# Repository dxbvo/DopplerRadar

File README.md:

# DopplerRadar
Development of a 24GHz Doppler radar system to measure the speed of a hockey puck. Developed using a STM32L476 Discovery board and a K-LC5 radar module from RFbeam Microwave.

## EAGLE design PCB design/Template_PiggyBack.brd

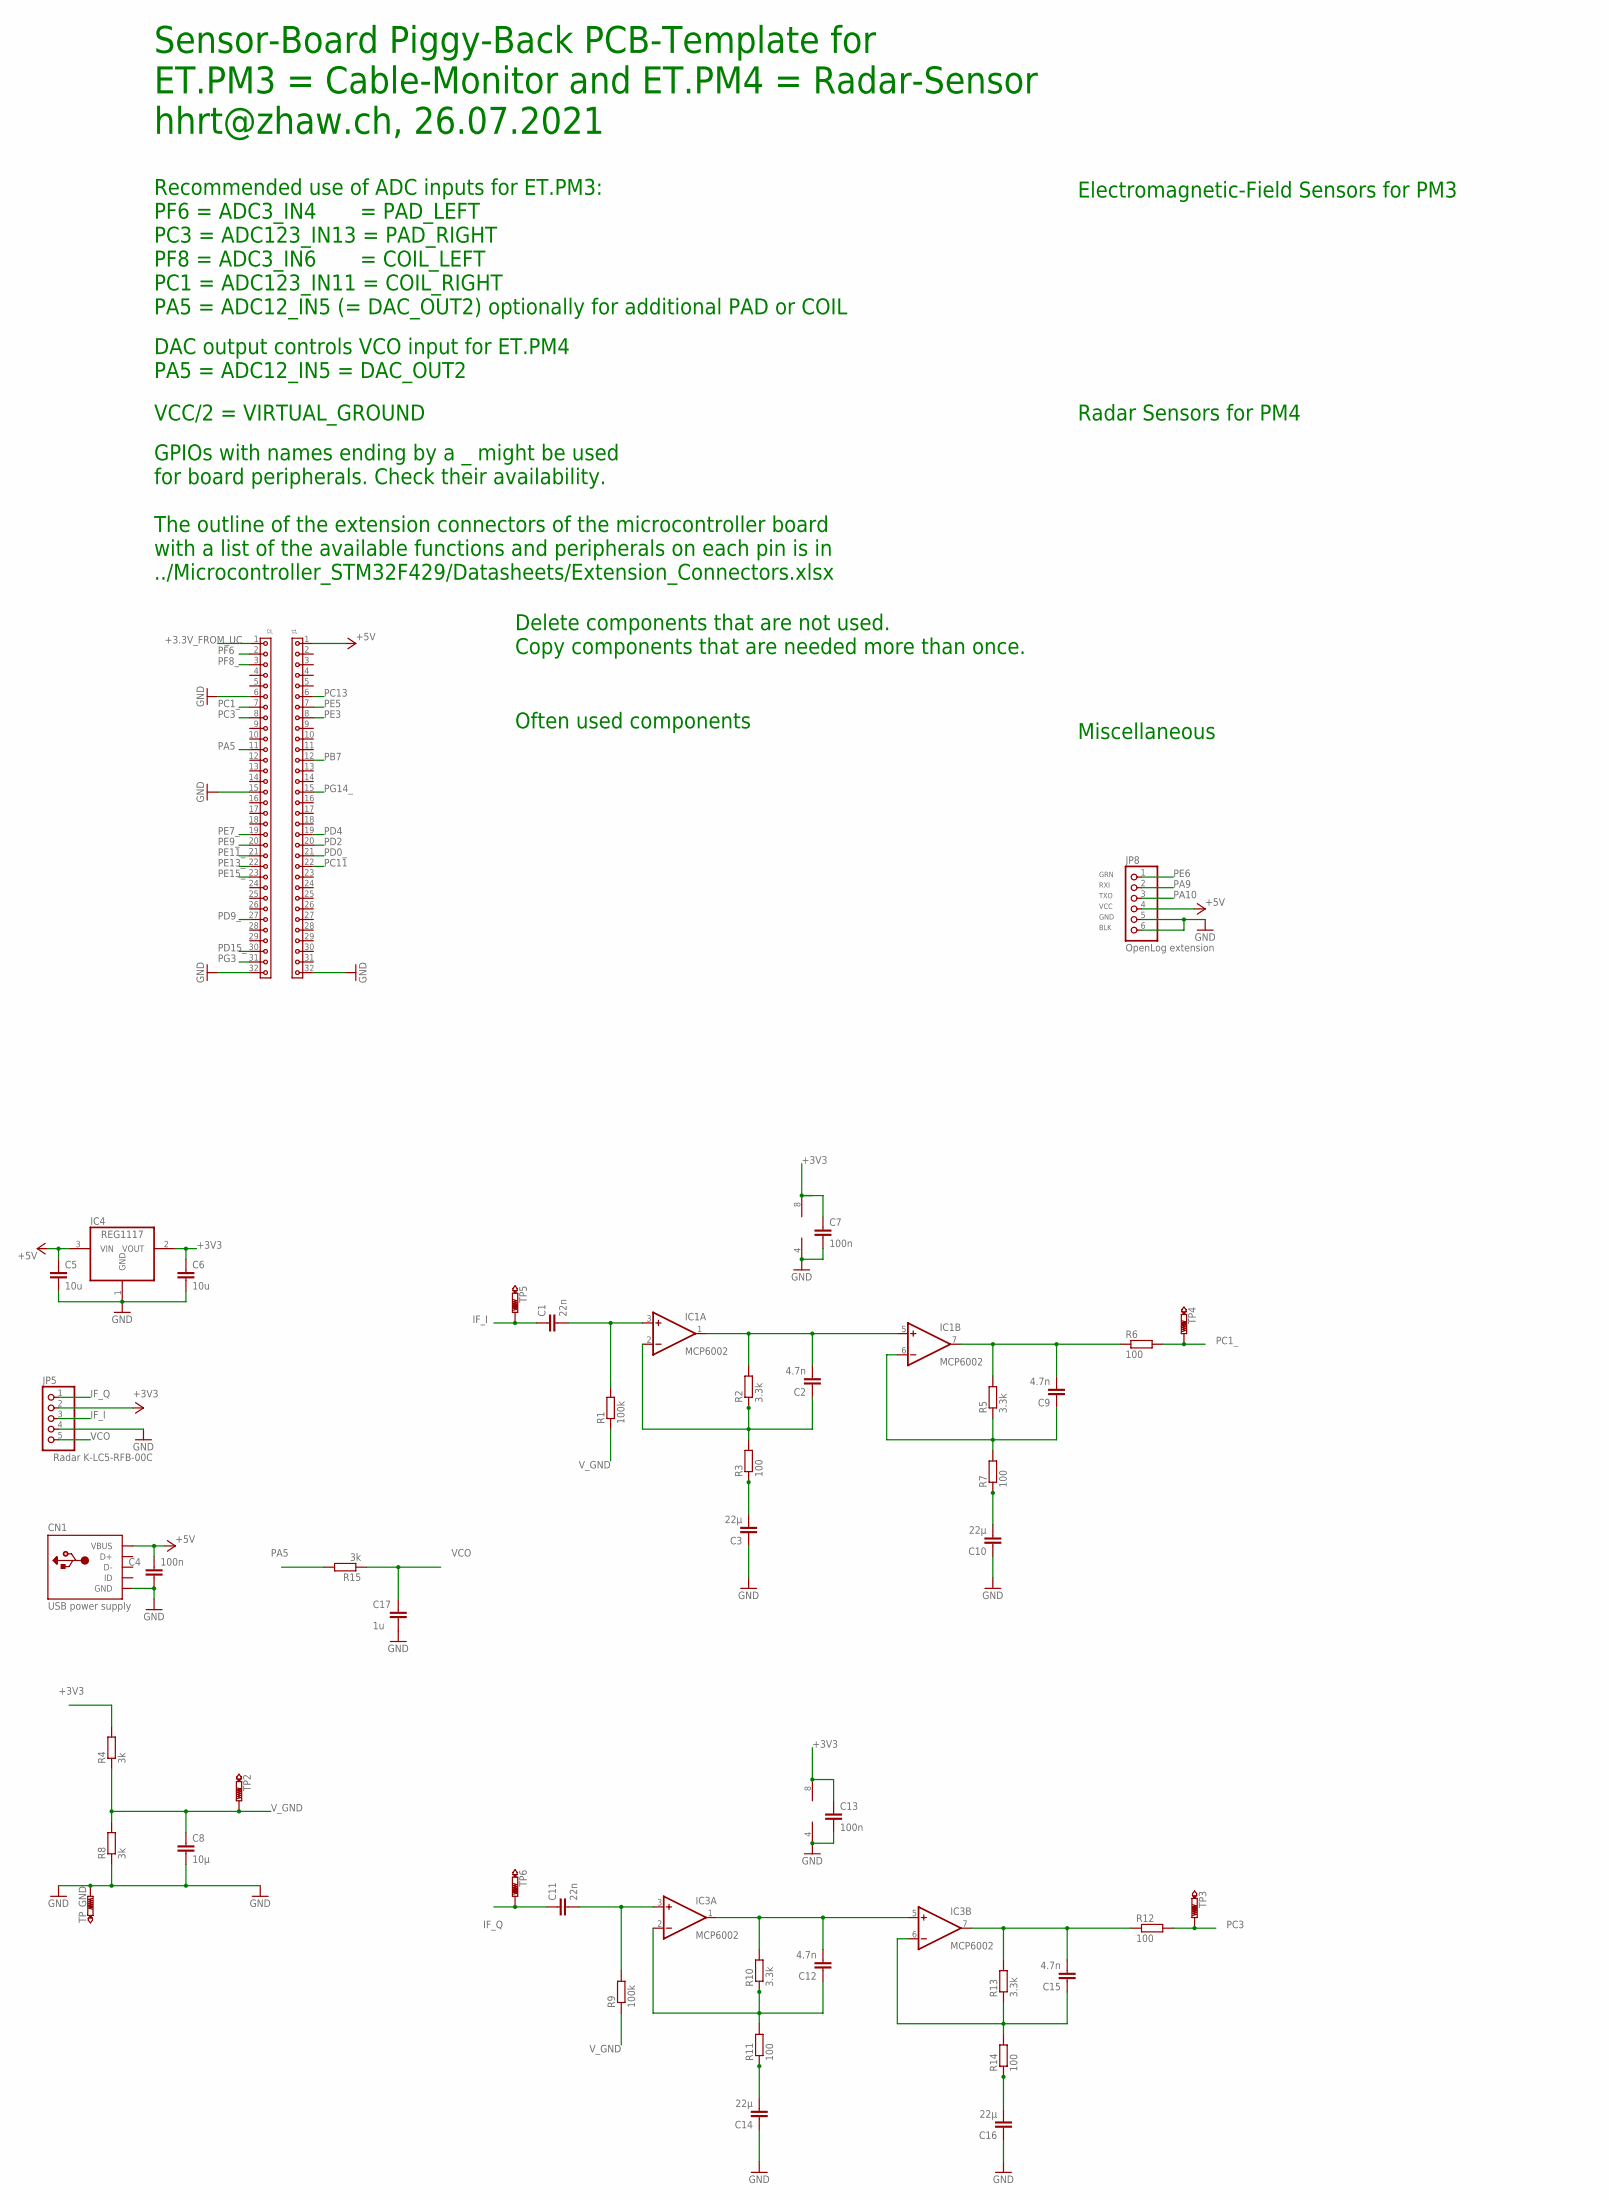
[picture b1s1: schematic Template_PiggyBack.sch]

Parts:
C1, C11: 22n; C1206
C2, C9, C12, C15: 4.7n; C0805
C3, C10, C14, C16: 22µ; C0805
C4, C7, C13: 100n; C0805
C5, C6: 10u; C0805
C8: 10µ; C0805
C17: 1u; C0805
CN1: USB power supply; USB-MINIB
IC1, IC3: MCP6002; SO08
IC4: REG1117; SOT223
J1, J2: 6130XX11821_61303211821; 61303211821
JP5: Radar K-LC5-RFB-00C; 1X05
JP8: OpenLog extension; 1X06
R1, R9: 100k; R0805
R2, R5, R10, R13: 3.3k; R0805
R3, R6, R7, R11, R12, R14: 100; R0805
R4, R8, R15: 3k; R0805
TP2, TP3, TP4, TP5, TP6: PTR1PAD1-17; P1-17
TP_GND: PTR1PAD1-17; P1-17

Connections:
+3.3V_FROM_UC: J2.1
+3V3: C6.1, C7.1, IC1.8 (V+), IC4.2 (VOUT), JP5.2, R4.2; also elsewhere on the board
+5V: C4.1, C5.1, CN1.VBUS, IC4.3 (VIN), J1.1, JP8.4
GND: C3.1, C4.2, C5.2, C6.2, C7.2, C8.2, C10.1, C13.2, C14.1, C16.1, C17.2, CN1.GND, IC1.4 (V-), IC3.4 (V-), IC4.1 (GND), J1.32, J2.6, J2.15, J2.32, JP5.4, JP8.5, JP8.6, R8.1, TP_GND.TP; also elsewhere on the board
IF_I: C1.1, JP5.3, TP5.TP
IF_Q: C11.1, JP5.1, TP6.TP
unnamed: C3.2, R3.1
unnamed: C2.1, IC1.2 (-IN), R2.1, R3.2
unnamed: C10.2, R7.1
unnamed: C1.2, IC1.3 (+IN), R1.2
unnamed: C2.2, IC1.1 (OUT), IC1.5 (+IN), R2.2
unnamed: C9.2, IC1.7 (OUT), R5.2, R6.1
unnamed: C9.1, IC1.6 (-IN), R5.1, R7.2
unnamed: C12.1, IC3.2 (-IN), R10.1, R11.2
unnamed: C16.2, R14.1
unnamed: C11.2, IC3.3 (+IN), R9.2
unnamed: C12.2, IC3.1 (OUT), IC3.5 (+IN), R10.2
unnamed: C15.2, IC3.7 (OUT), R12.1, R13.2
unnamed: C15.1, IC3.6 (-IN), R13.1, R14.2
unnamed: C14.2, R11.1
PA5: J2.11, R15.2
PA9: JP8.2
PA10: JP8.3
PB7: J1.12
PC1_: J2.7, R6.2, TP4.TP
PC3: J2.8, R12.2, TP3.TP
PC11: J1.22
PC13: J1.6
PD0_: J1.21
PD2: J1.20
PD4: J1.19
PD9_: J2.27
PD15_: J2.30
PE3: J1.8
PE5: J1.7
PE6: JP8.1
PE7_: J2.19
PE9_: J2.20
PE11_: J2.21
PE13_: J2.22
PE15_: J2.23
PF6: J2.2
PF8_: J2.3
PG3: J2.31
PG14_: J1.15
VCC: C13.1, IC3.8 (V+)
VCO: C17.1, JP5.5, R15.1

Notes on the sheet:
GPIOs with names ending by a _ might be used for board peripherals. Check their availability.
Sensor-Board Piggy-Back PCB-Template for ET.PM3 = Cable-Monitor and ET.PM4 = Radar-Sensor hhrt@zhaw.ch, 26.07.2021
Recommended use of ADC inputs for ET.PM3: PF6 = ADC3_IN4 = PAD_LEFT PC3 = ADC123_IN13 = PAD_RIGHT PF8 = ADC3_IN6 = COIL_LEFT PC1 = ADC123_IN11 = COIL_RIGHT PA5 = ADC12_IN5 (= DAC_OUT2) optionally for additional PAD or COIL
The outline of the extension connectors of the microcontroller board with a list of the available functions and peripherals on each pin is in ../Microcontroller_STM32F429/Datasheets/Extension_Connectors.xlsx
VCC/2 = VIRTUAL_GROUND
GRN
RXI
TXO
VCC
GND
BLK
Often used components
Electromagnetic-Field Sensors for PM3
Radar Sensors for PM4
Miscellaneous
DAC output controls VCO input for ET.PM4 PA5 = ADC12_IN5 = DAC_OUT2
Delete components that are not used. Copy components that are needed more than once.

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
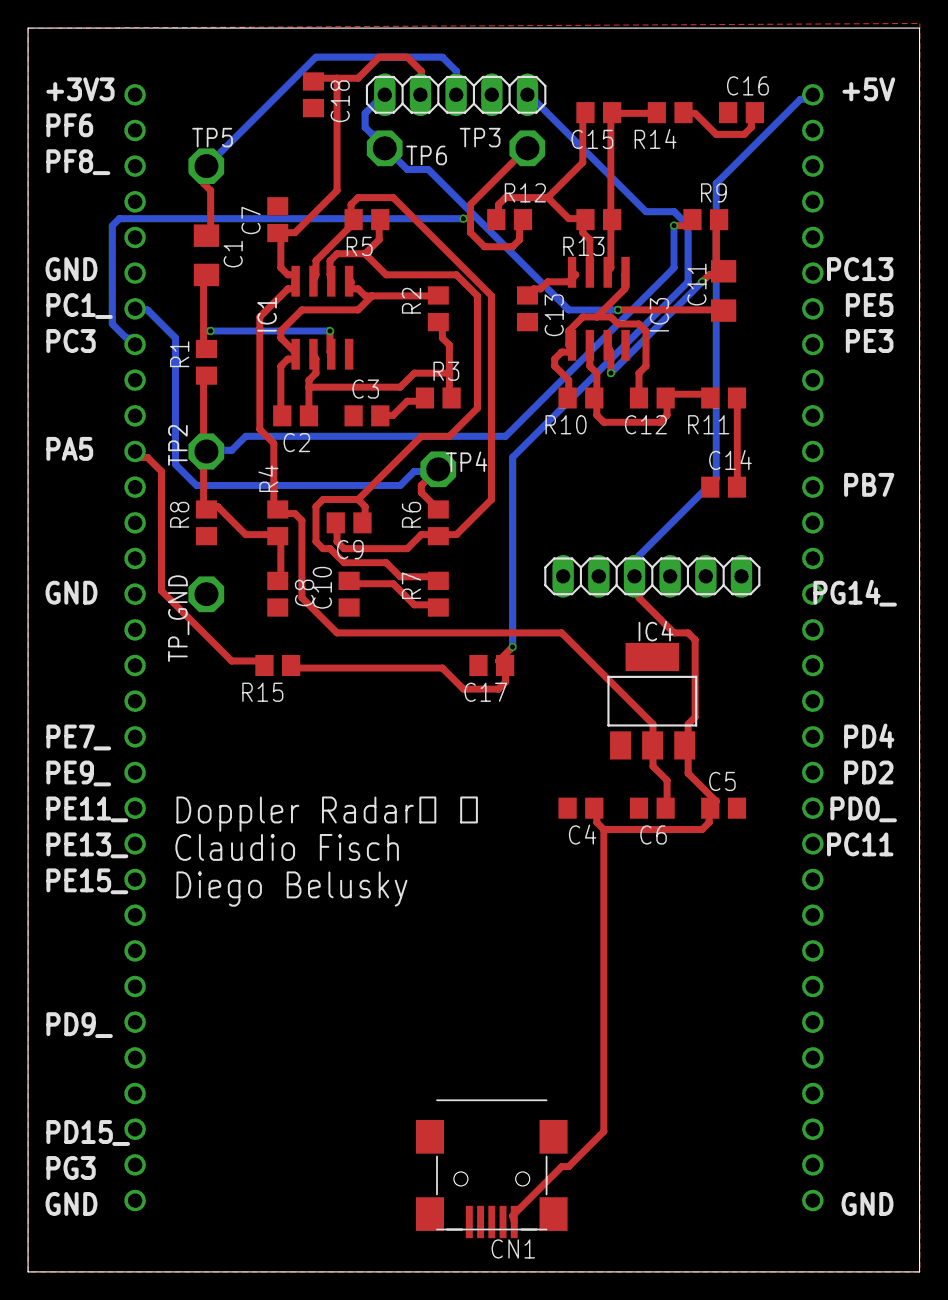
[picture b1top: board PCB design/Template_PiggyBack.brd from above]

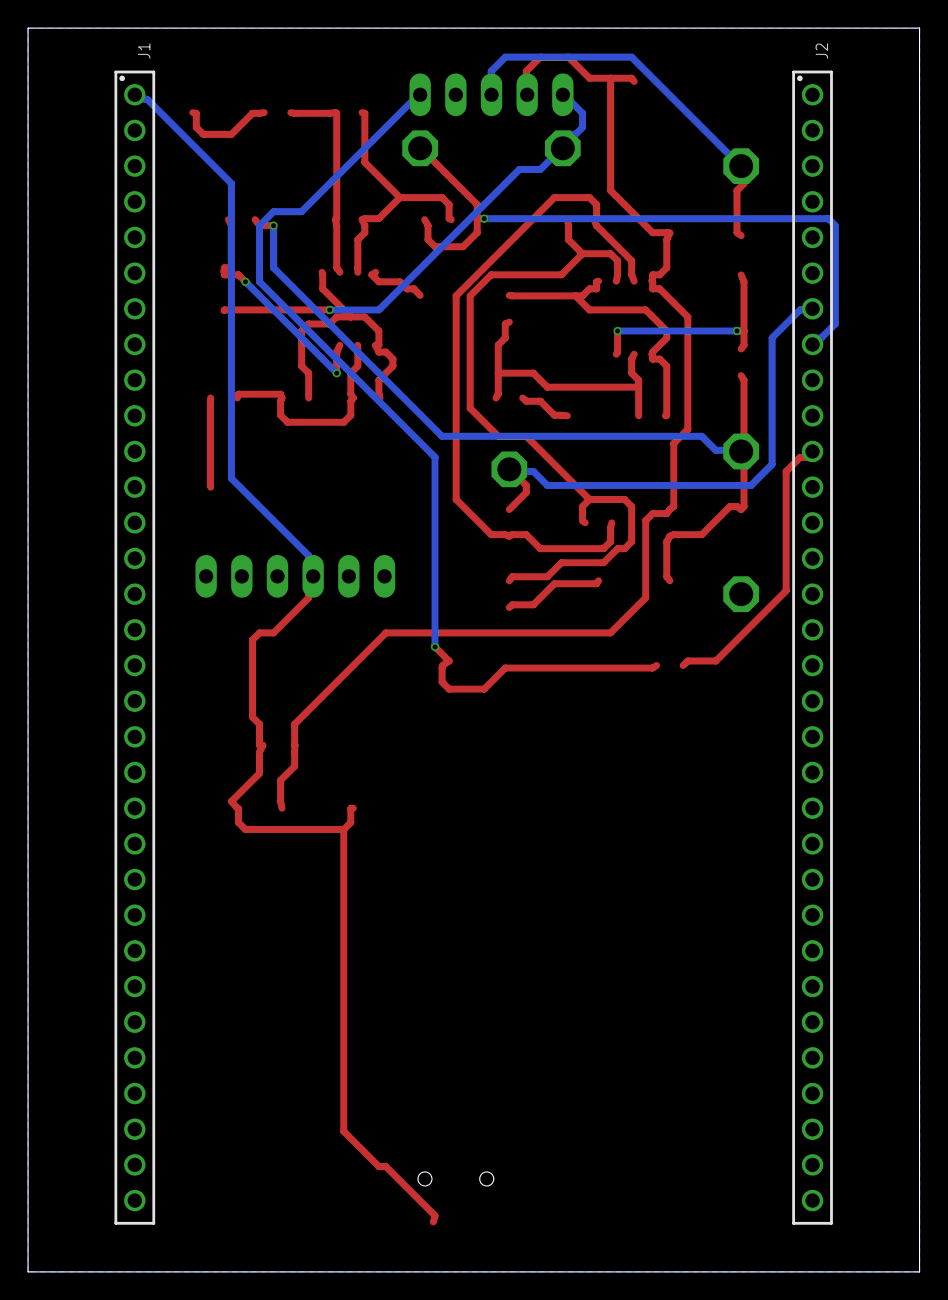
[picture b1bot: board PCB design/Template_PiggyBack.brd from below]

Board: 2 copper layers, 63.5 x 88.6 mm, 47 parts (2 on the bottom side), 25 nets.

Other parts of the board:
C18: 100n; C0805

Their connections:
+3V3: C18.1; also elsewhere on the board
GND: C18.2; also elsewhere on the board

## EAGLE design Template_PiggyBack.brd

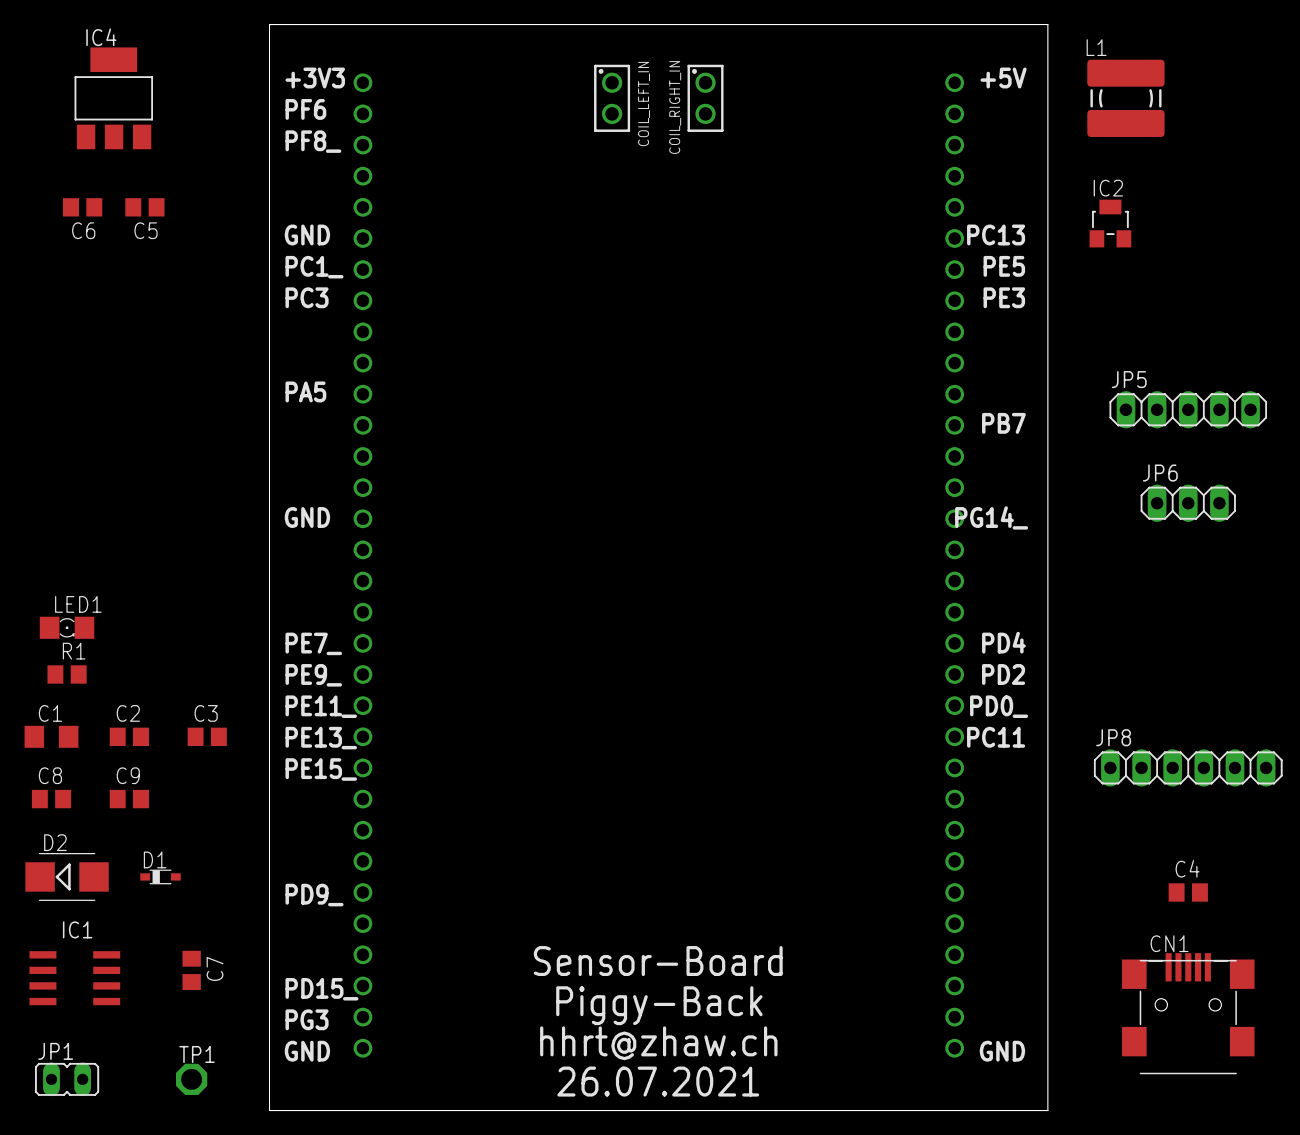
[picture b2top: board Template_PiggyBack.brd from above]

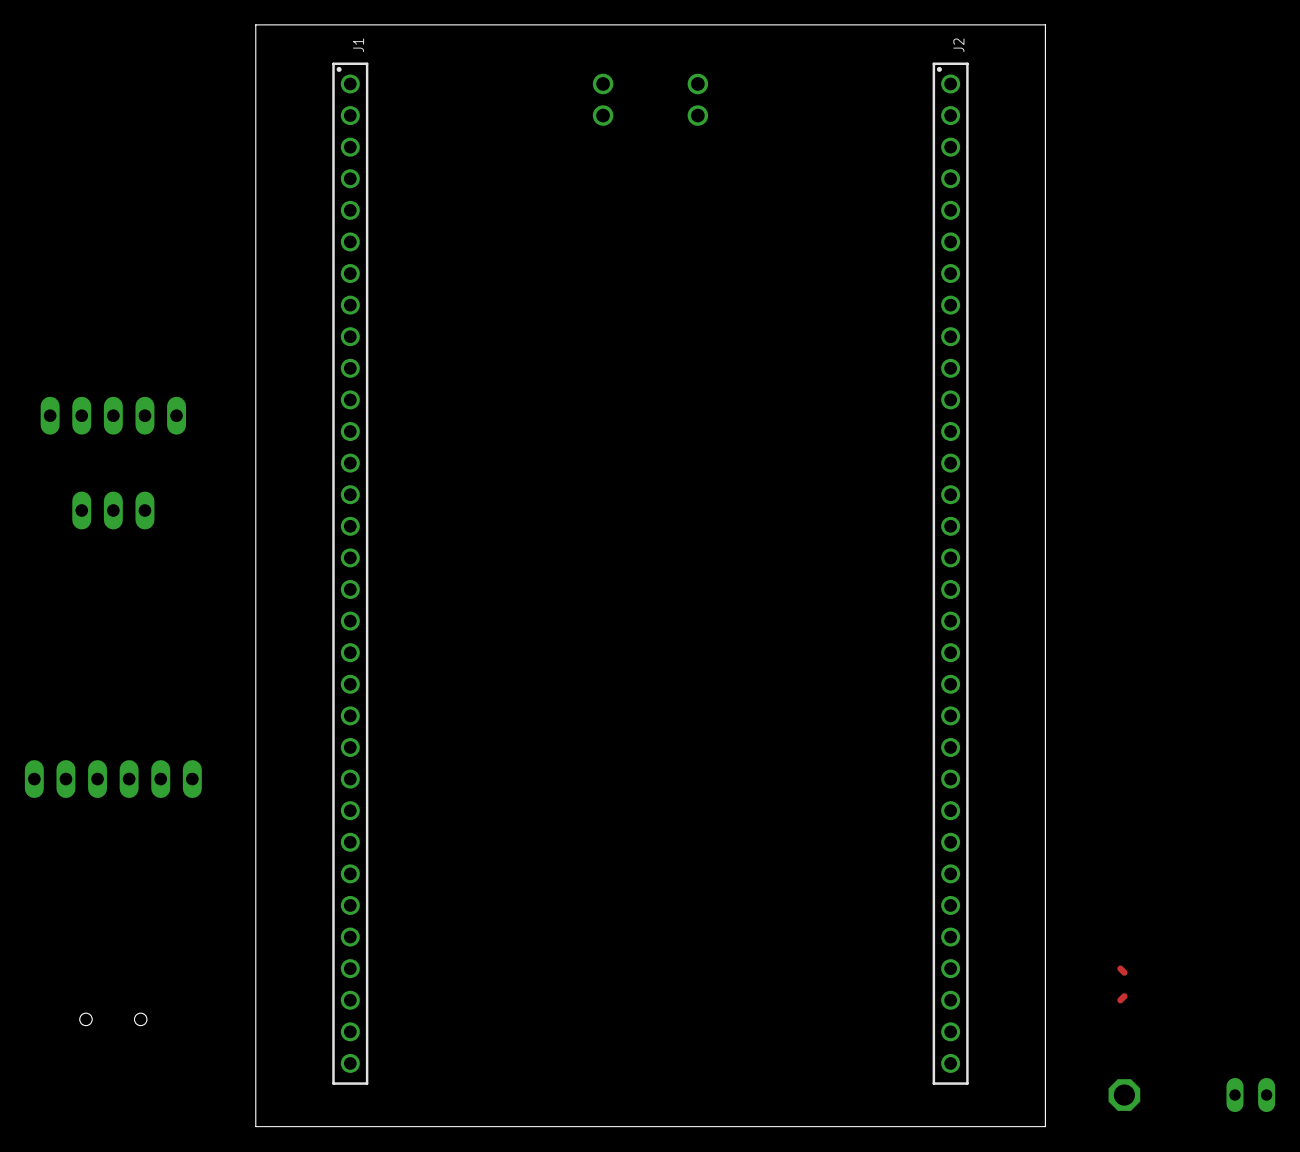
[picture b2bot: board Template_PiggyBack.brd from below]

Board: 2 copper layers, 63.5 x 88.6 mm, 27 parts (2 on the bottom side), 4 nets.

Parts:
C1: 100u; C1206
C2, C5, C6: 10u; C0805
C3, C4: 1u; C0805
C7, C8: 100n; C0805
C9: 10n; C0805
CN1: USB power supply; USB-MINIB
COIL_LEFT_IN: 61300211121
COIL_RIGHT_IN: 61300211121
D1: SD103; SOD323_ST
D2: SL13; SMB
IC1: MCP6002; SO08
IC2: Hall-Sensor-DRV5053VA; SOT23-W
IC4: REG1117; SOT223
J1, J2: 61303211821
JP1: JP1
JP5: Radar K-LC5-RFB-00C; 1X05
JP6: Mounting support for K-LC6; 1X03
JP8: OpenLog extension; 1X06
L1: Coil-Sensor-15mH; POWER-CHOKE_WE-TPC
LED1: LED_1206
R1: R0805
TP1: PTR1PAD1-17; P1-17

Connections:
+3V3: C6.1, IC4.2, JP5.2
+5V: C4.1, C5.1, CN1.VBUS, IC4.3, J1.1, JP8.4
GND: C4.2, C5.2, C6.2, C7.2, CN1.GND, IC1.4, IC2.3, IC4.1, J1.32, J2.6, J2.15, J2.32, JP5.4, JP8.5, JP8.6
unnamed: C7.1, IC1.8

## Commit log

2023-03-19 cleaned working space
2023-03-20 Original Circuit
    changed circuit for PCB Layout
2023-03-20 added capacitors to .brd-file
2023-03-21 added layout
2023-03-21 circuit sketch done
2023-03-22 Circuit
    with correct values
    OP still not exactly the same as in Eagle
2023-03-22 worked on pcb layout
2023-03-23 PCB Output
    changed the PCB Output to PC1 and PC3
2023-03-23 finished layout but it is subject to revision
2023-03-23 stil some errors in the layout because of width
2023-03-23 layout mission complete
2023-03-24 better layout version
2023-03-24 errors in layout fixed
2023-03-25 adapted layout according to Rennhard's feedback
2023-03-26 GND plate added
2023-03-26 errors fixed
2023-03-28 layout done
2023-03-29 added Firmware
2023-03-29 folder structure
2023-04-05 changed some values in schematic
2023-04-05 Firmware set up
2023-04-06 worked on fft
2023-04-12 worked on fft. Error when trying to display on STM because of plotting the values
2023-04-17 calculating velocity from test array worked
2023-04-18 worked on GUI
2023-04-22 worked on fft...
2023-04-22 cleaned up Test folder
2023-04-24 added video script
2023-04-25 rennhard changes
    changed cast and bitreversal
    (bin0) = 0 fehlt noch
2023-04-25 fft test
    änderung in FFT_Test.m
    (sig Array war noch zu gross)
    fft funktioniert.
    kleine Änderungen in measurin und main.c
2023-04-25 FFT should be correct now
2023-04-25 worked on video script
2023-04-26 still on fft
2023-05-02 ADC_samples
    - changed ADC_samples to 2*ADC_NUMS
2023-05-02 Tests
    Tests with TestData positiv and negative passed
    - 10km/h difference... why?
2023-05-02 new fftInOut
    test with hardware dont work!
2023-05-03 test Output debug
    added matlab file to tests
2023-05-03 test done
    test done
2023-05-07 implemented array for data transfer
2023-05-10 refactored code
2023-05-10 THRESHOLD
    mean function implemented
2023-05-12 HighScore
    - implemented HighScore
    - small changes in display
    Note: Reset highscore value is missing
2023-05-12 Optimize Treshold and testOutput
    - changed TRESHOLD and testOutput for better measurments.
    still not where we want to be
2023-05-15 VideoScipt Matic
    corrected version
2023-05-24 added Demonstration File
2023-05-24 Timetable
    adjustments
2023-05-27 tried some UART
2023-06-02 demo script modified
2023-06-02 Treshold
    treshold to 200

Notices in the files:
parts and their libraries:
Wurth_Connectors_WR-PHD: Copyright: Würth Elektronik
